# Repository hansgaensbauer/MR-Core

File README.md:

### __Quick Start:__ The [software](/software) folder contains a template Jupyter Notebook and documentation for the MRC class. 

# MR-Core
An FPGA Driven DAC + ADC for Magnetic Resonance, intended as a capable controller for Magnetic Resonance Imaging and Magnetic Resonance Relaxometry. 

### Features
- STM32F767 Microcontroller for experiment-level sequencing and backend signal processing
- Artix 7 FPGA for pulse generation, digital downconversion and DSP
- 500MSps dual oversampling DAC with on-chip NCO for RF pulse synthesis
- 120MSps dual ADC
- X, Y, and Z gradient drivers for 3A low impedance gradient coils
- 5Gbps USB-3.0 controller for raw data extraction
- 100/10 Ethernet 
- SD Card Interface
- Magnet/switch interface for temperature control and T/R switching

# User Manual

## Repository Setup and Software Prerequisites
### Required Software
- [KiCAD EDA](https://www.kicad.org/)
- [STM32CubeIDE](https://www.st.com/en/development-tools/stm32cubeide.html)
    - [STM32CubeF7 Package](https://www.st.com/en/embedded-software/stm32cubef7.html) Version 1.7.1 or 1.7.2
    - ARM CMSIS 5.4.0
- [AMD Vivado](https://www.xilinx.com/products/design-tools/vivado.html)

</br>
To set up the KiCAD Libraries:

- Open KiCAD, go to Preferences -> Configure Paths..., and add a new Environment Variable called "BioMEMS" that points to the hardware/Library folder. 
- Add the symbol library by selecting Preferences -> Manage Symbol Libraries... and selecting the BioMEMS.kicad_sym file in this folder. 
- Check that the library path shows up as "${BioMEMS}.kicad_sym". 
- Add the footprint library by selecting Preferences -> Manage Footprint Libraries... and selecting the BioMEMS.pretty folder in Library. 
- Check that the library path uses the ${BioMEMS} variable.

</br>
The STM32CubeIDE project requires similar setup:

- Create an environment variable called STM32CUBE_REPO, pointed to the STM32Cube\Repository folder on your computer.
- Restart your computer
- Open the project in STM32CubeIDE, and navigate to the IOC file
- Under "Software Packs", click "Manage Software Packs"
- Click "From URL", then "New"
- Add the URL "https://raw.githubusercontent.com/STMicroelectronics/STM32CubeF7/master/Drivers/CMSIS/ARM.CMSIS.pdsc"
- Click "OK" (several times) to add the software pack.
- You may have to close and reopen the "Manage Software Packs" window
- Click the "ARM" tab, and check "CMSIS 5.4.0"
- Click "OK" to close the window, then click "Select Components" under "Software Packs"
- Expand ARM.CMSIS, and check "CMSIS Core - 5.1.2" and "CMSIS DSP 1.5.2" 
- Click OK
- Under Middleware and Software Packs, click "CMSIS", and make sure both CMSIS Core and DSP are checked in the panel that opens
- Save the IOC and rebuild the code
- To add the STM32CubeF7 repository, extract the STM32CubeF7 to the STM32CUBE_REPO folder (next to "Packs")
- Pull the STM32Cube_FW_F7_V1.17.X folder out so it's at the same level as the Packs folder. Check that the path to this folder matches the include paths in Project->Properties (you may have to rename the folder or adjust the paths).

## Hardware Description
### Open Assembly

### PCB Connector Diagram

## Powering On
The MR-Core is designed to work with a 13.8V DC power supply, such as those sold by [Astron Corporation](https://www.astroncorp.com/). These are commonly used for amateur radio, but any linear power supply capable of providing 10A continuously is suitable. If the gradients are not used, only 3A are required. The power connector is a [ASMPR45-1X2-RK](https://www.digikey.com/en/products/detail/anderson-power-products-inc/ASMPR45-1X2-RK/13150596) from [Anderson Power Products, Inc.](https://www.andersonpower.com/us/en.html).

## Programming
### Programming the Microcontroller
- Connect an ST-Link programmer to the STM32 SWD port on the MRC. 
- Flash using STM32CubeIDE

### Programming the FPGA
- Connect an AMD compatible JTAG cable to the FPGA JTAG port on the MRC.
- Open the Hardware Manager in Vivado
- Click "Auto Connect"
- Click "Program" and select the .bit file for the FPGA

### Programming the SPI Flash
By default, new designs programmed into the FPGA must be reprogrammed every time the device loses power. To allow the FPGA image to persist between reboots, a SPI configuration flash is included that can program the FPGA with a default image on startup. To change this default image:
- Right click on create bitstream
- Click "bitstream settings"
- Check the ".bin" option
- Click Apply
- Generate the bitstream
- Click "Add Configuration Memory Device"
- If prompted, search for and select "IS25LP256"
- Right click on the device
- Click "Program"
- find .bin file in runs->impl_1 folder
- Select "Pull-Ups"
- Select the "Erase", "Program", and "Verify" options
- Select Apply, OK
- Disconnect the programming cable and restart the FPGA.

To program the SPI flash without changing the configuration (which you will want to do in most cases to update the FPGA image), the steps are more simple.
- In the Hardware Manager, right click on the SPI Flash in the Hardware window.
- Click "Program Configuration Memory Device"

## Analog Frontend (AFE)
The AFE for the MRC consists of two SXLP-21.4+ lowpass filters and two ZX60-43-S+ gain block amplifiers for the receive side, and one ZX60-100VHX+ amplifier for transmit. The amplifiers are powered by connectors from the MRC PCB, and should not be used with the heatsink removed. The transmit amplifier may be destroyed if it transmits into a poorly tuned or disconnected probe. For development, the transmit port of the MRC should be connected to a 50 ohm termination. The filters can be bypassed by soldering an 0603 resistor onto the jumpers on the filter PCBs. The MRC AFE is intended to be used with an external switch and preamplifier located on the probe - the gain blocks are not low noise amplifiers. 

## Magnet Interface
The magnet interface is connected to the MRC using an ethernet cable. The interface exposes FPGA IO for switching, as well as 3.3V power and microcontroller IO for general use. 

## Gradients
The gradients use 1/4" TRS audio connectors. Do not use 1/4" mono connectors, and do not insert or remove the connectors for the gradients when the board is powered. Doing so can damage the gradient drivers. The gradients are driven by H-bridge circuits to the supply voltage, current limited to 3A by three power resistors on the board. For this reason, neither contact for the gradients (Tip or Ring) is grounded. The Shield should not be connected to the gradient coil.

## USB 3.0
Support for direct baseband sample streaming with Steam-O-Scope firmware from [Joseph Feld](https://github.com/JosephFeld).

## Switch/Preamplifier Module

In order to make it possible to use non-MRC compatible probes with the MRC, a switch and preamplifier module is provided. This module provides about 10dB of gain and it includes a ZX80-DR230-S+ absorbtive RF switch. The truth table for the switch is:
| SW[1]  | SW[0] | Switch State |
| ------------- | ------------- | ----- |
| 0  | 0  | Both Off |
| 0  | 1  | Receive |
| 1  | 0  | Transmit |
| 1  | 1  | Unknown |

The yellow LED on the preamplifier module ethernet connector indicates the status of the transmit switch (on = closed) and the green LED likewise indicates the status of the receive switch.

## MRR-Core Image
This image implements a general purpose, programmable controller for MRI sequences. 

The system is programmed by the STM32 over SPI, and each SPI transaction is 16 bits with the MSB first. There are three types of SPI command: control register programming, frequency tuning word programming, and sequence programming. 

The control register is used for general purpose control of the FPGA, and can be accessed with a SPI transaction where bits [15:14] are `0b10`. The 8 LSBs give the new control register value. The control register is shown below:
**CMD (Opcode `0b00`)**
```
[  7  |  6  |  5  |  4  |  3  |  2  |  1  |  0  ]
[ RST |     |     |     |     |     |TRIG |     ]
```

To program the 16 bit frequency tuning word, the system must first be put into frequency tuning mode by sending the frequency tuning command `0xC000`. The frequency tuning word is sent on the next transaction, and the system will automatically return to IDLE afterward.

To enter sequence programming, the sequence programming command must be sent with the number of lines in the sequence program. The programming command starts with `0b00`, and the 14 LSBs are the number of 16 bit instructions in the sequence.

### MRC Instruction Set
The MRC uses a very simple instruction set designed for precise execution of any pulse sequences. There are four instructions:

**CMD (Opcode `0b00`)**
```
[ 15 | 14 | 13 | 12 | 11 | 10 |  9 |  8 |  7 |  6 |  5 |  4 |  3 |  2 |  1 |  0 ]
[  0 |  0 |   AMP   |  PHASE  |   GRX   |   GRY   |   GRZ   |      RESERVED     ]
```
Change the transmitter amplitude and phase to the values indexed by AMP and PHASE. Set the gradients to the values set by GR[xyz].

**LSET (Opcode `0b01`)**
```
[ 15 | 14 | 13 | 12 | 11 | 10 |  9 |  8 |  7 |  6 |  5 |  4 |  3 |  2 |  1 |  0 ]
[  0 |  1 | COUNTER |                          VALUE                            ]
```
Set COUNTER to VALUE.

**JMP (Opcode `0b10`)**
```
[ 15 | 14 | 13 | 12 | 11 | 10 |  9 |  8 |  7 |  6 |  5 |  4 |  3 |  2 |  1 |  0 ]
[  1 |  0 | COUNTER |                         ADDRESS                           ]
```
If COUNTER is not zero, jump to the absolute ADDRESS. If COUNTER is zero, set COUNTER to `0xFFFF` and advance the instruction counter.

**HALT (Opcode `0b11`)**
```
[ 15 | 14 | 13 | 12 | 11 | 10 |  9 |  8 |  7 |  6 |  5 |  4 |  3 |  2 |  1 |  0 ]
[  1 |  1 |                                                                     ]
```
Terminates the sequence.

To better compress the immediates for programming amplitude and phase so that all of the pulse parameters can be updated simultaneously, the AMP and PHASE fields in the CMD instruction do not directly specify the amplitude or phase, but instead give the address of the correct value within separate lookup tables that are programmed with the sequence. The first four lines of the sequence program are the four amplitude fields, and the second four lines are the four phase fields. 

### Digital Downconversion
The 120MSps data stream from the ADC is too much data for the STM32 to process, and most of this data is useless as it covers frequencies far away from the Larmor frequency of the magnet. To lower the data rate and isolate only a certain band of interest, the FPGA can digitally downconvert and downsample the ADC data stream. The digital design responsible for this is contained in the "mrr-ddc" block design within the MR-Core Vivado project. 

The structure of the DDC is shown in the HDL block diagram above. The parallel data is converted to AXI by the adc_to_axi module. This is fed into the mrr-ddc block design, which includes a complex multiplier and direct digital synthesizer for downconversion. The frequency shifted products are filtered and passed to a FIFO, before being passed to the STM32 using the STM32 Flexible Memory Controller (FMC).

The layout of the digital filter is shown below:

This filter is responsible for both decimation and the bulk of noise rejection, so the performance requirements are strict. The filter is implemented in several stages so that the high complexity FIR filters at the end see only data streams that are already significantly decimated (the final FIR filter sees an input data rate of 1MSa/s, compared to 120MSa/s for the CIC decimator).

The filter design is done in Matlab, and the current design is captured by filtdesign.m in MR-Core->hdl->Utilities. The transfer function is shown below (x axes in MHz):

## Firmware
The firmware running on the STM32 is responsible for processing or passing the data stream from the FPGA during receive, and also for configuring the FPGA, the DAC, and the ADC. The mrc STM32CubeIDE project in the "firmware" folder provides C drivers for the DAC, the ADC, and an "MRC" driver that handles communication with the FPGA, pulse sequencing, and data streaming. The DAC and ADC drivers provide access to the test patterns, power down states, and programming registers for these chips.

For USB 2.0 Full speed data streaming, the `Transfer_Buffer()` function in mrc.c will coordinate FMC reads into a ping-pong buffer that is then emptied over the USB CDC hardware into a PC. A basic serial command interface is available in this demo so that a user can trigger pulse-echo sequences by sending the command `pulseecho` over USB CDC.

## Software and UI
### Pulseq Compiler
A limited Pulseq compiler is provided in `software`. This program requires pypulseq to run, however, the latest stable release of pypulseq cannot run with the most recent versions of numpy. This can be solved by replacing every instance of `np.float` and `np.complex` in the sigpy and pypulseq libraries with `float` and `complex` respectively. 

To run the compiler, use `py mrc_pulseq_assembler.py [sequence_file.seq]` where `[sequence_file.seq]` is replaced by the path to your pulseq file. This will generate a .mrc file with the machine code for the MRI. To facilitate debugging, a objdump-style disassembler is also provided. To run the disassembler, use `py mrcdump.py [mrc_file.mrc]` where `[mrc_file.mrc]` is replaced with the path to your .mrc file. It will produce an output in the following format:

```
Statics:
Phase 0: 0
Phase 1: 0
Phase 2: 0
Phase 3: 0

Amp 0: 0
Amp 1: 28000
Amp 2: 56000
Amp 3: 0

Instructions:
0:      0001000000000000        cmd     1 0 00 00 00
1:      0100010010101111        lset    0 1199
...     ...                     ...     ...
20:     0000000000000000        cmd     0 0 00 00 00
21:     1100000000000000        halt.
```

For the system demo, a python driver for the MRC board is available in the "software" folder. bioreactormonitoring.py uses this driver to periodically acquire pulsecho sequences and plot the received data and extracted T2 values on an animated graph on the computer.

## Contributing
Best practices: make your own branch!

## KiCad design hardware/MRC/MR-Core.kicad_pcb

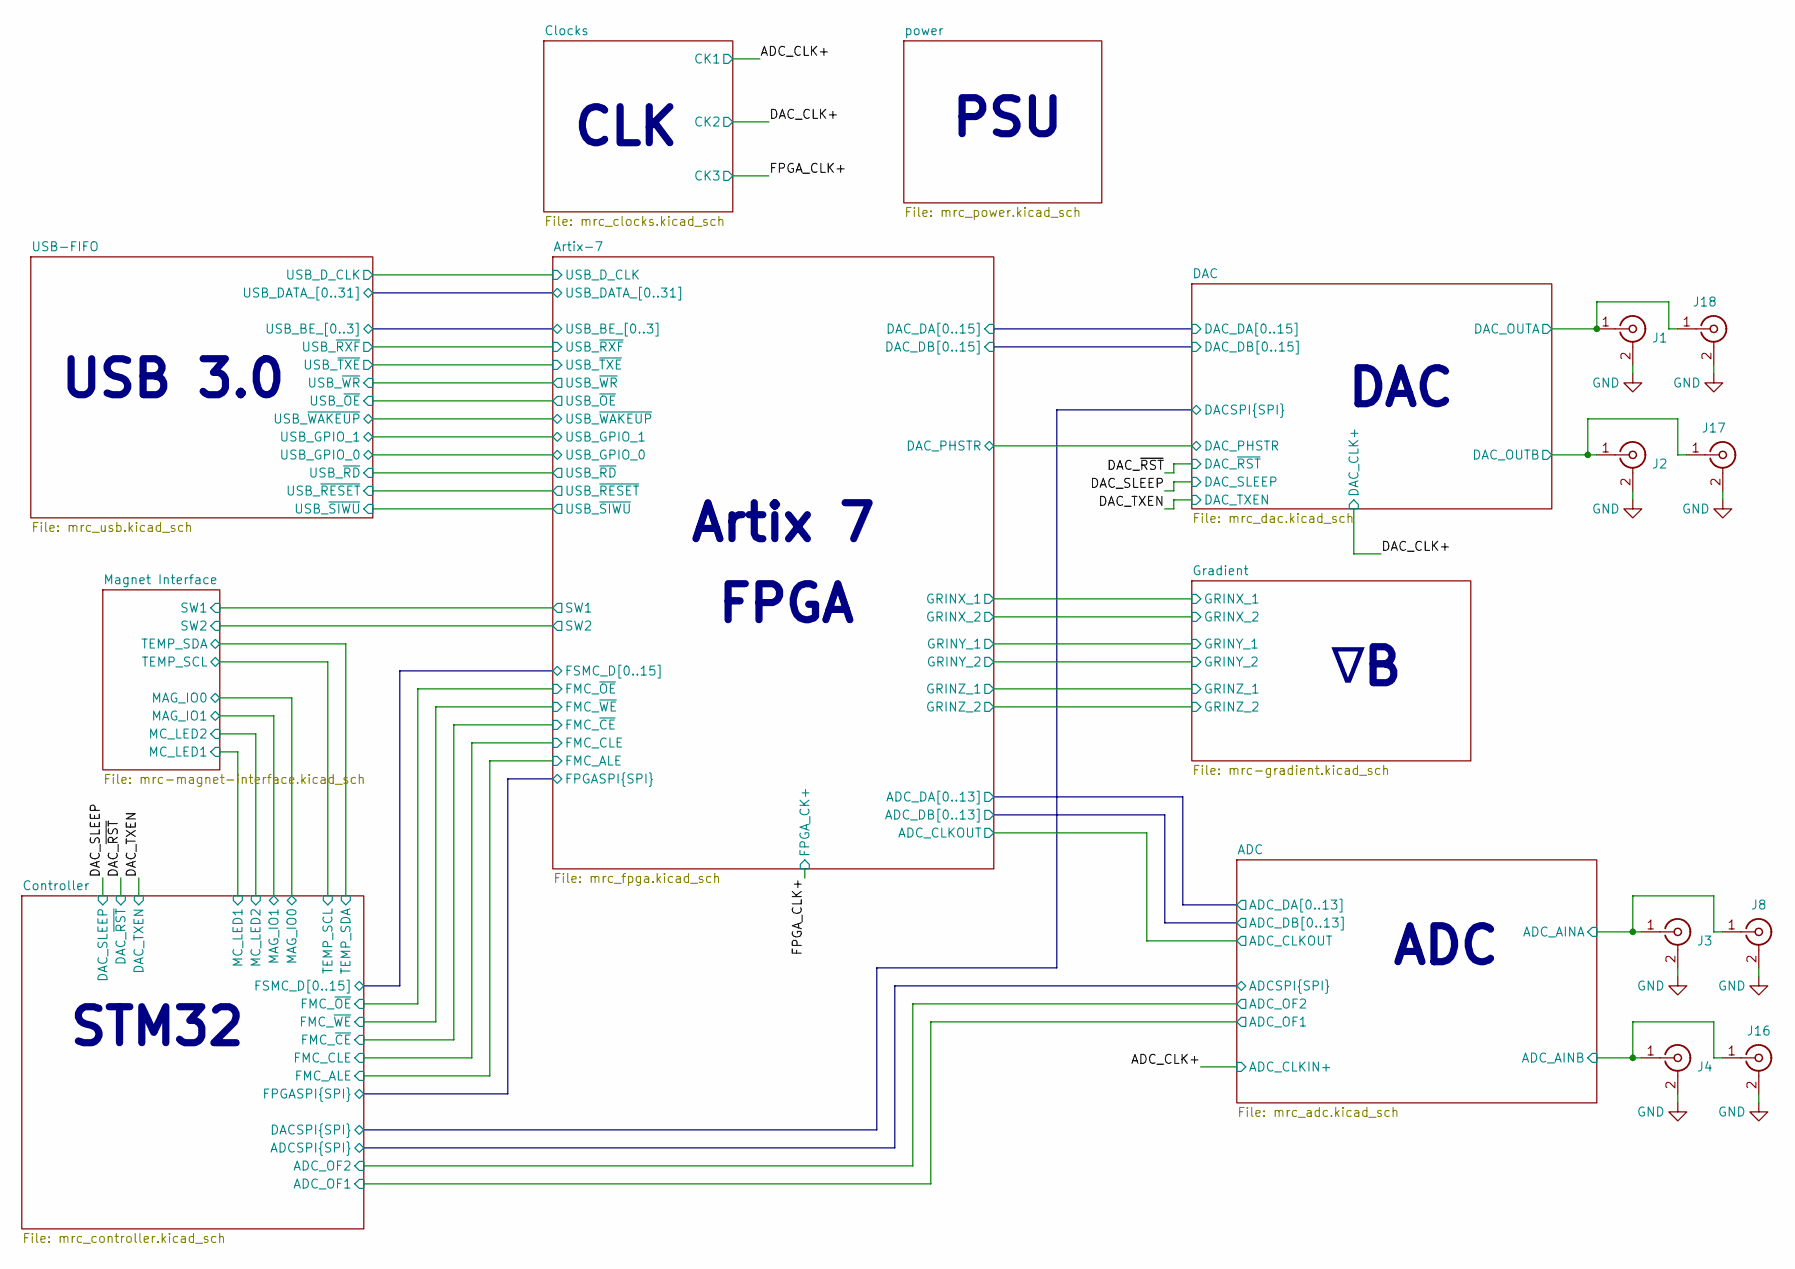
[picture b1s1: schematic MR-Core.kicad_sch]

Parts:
J1, J2, J3, J4: Conn_Coaxial; MMCX_Molex_73415-1471_Vertical; MPN C588477
J8, J16, J17, J18: Conn_Coaxial; SMA_Samtec_SMA-J-P-X-ST-EM1_EdgeMount; MPN C588477

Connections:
/ADC/ADC_AINA: J3.1 (In), J8.1 (In); also elsewhere on the board
/ADC/ADC_AINB: J4.1 (In), J16.1 (In); also elsewhere on the board
/DAC/DAC_OUTA: J1.1 (In), J18.1 (In); also elsewhere on the board
/DAC/DAC_OUTB: J2.1 (In), J17.1 (In); also elsewhere on the board

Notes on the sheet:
FPGA
USB 3.0
ADC
Artix 7
STM32
CLK
DAC
PSU

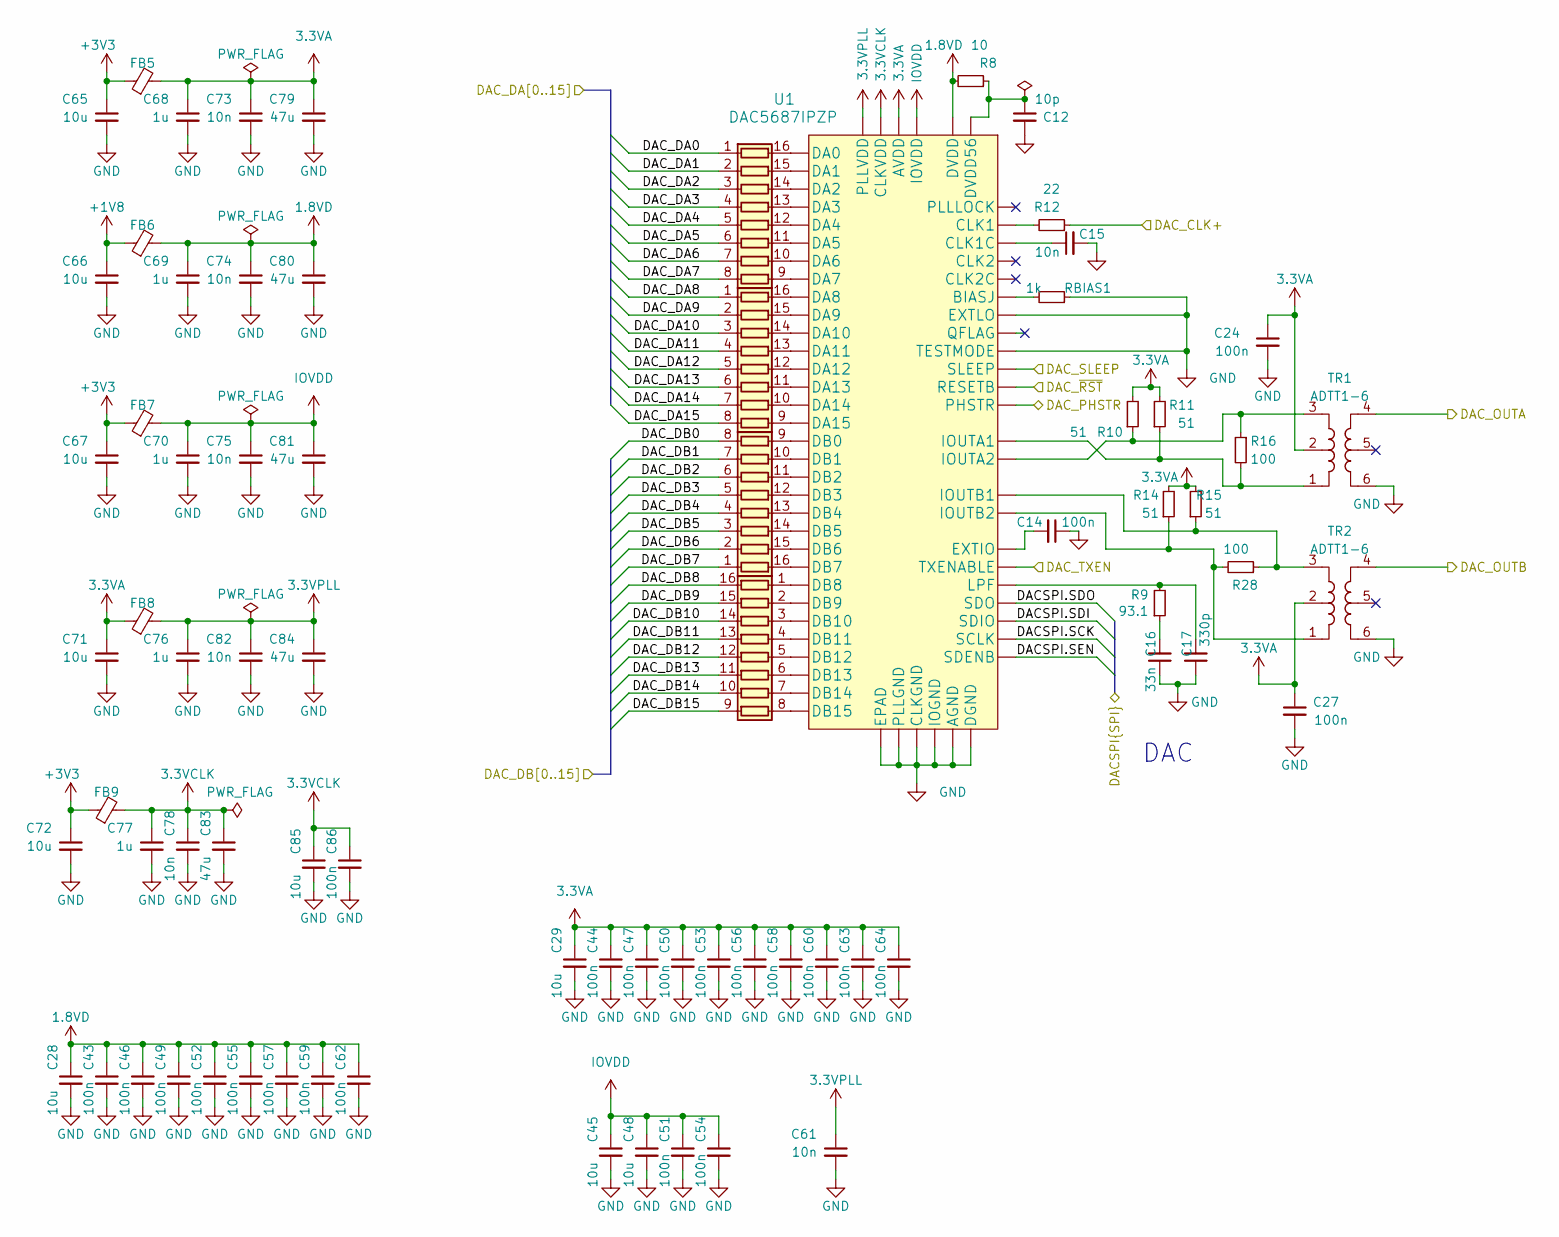
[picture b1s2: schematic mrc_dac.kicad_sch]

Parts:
C12: 10p; C_0603_1608Metric; MPN C1634
C14, C24, C27, C43, C44, C46, C47, C49, C50, C51, C52, C53, C54, C55, C56, C57, C58, C59, C60, C62, C63, C64, C86: 100n; C_0603_1608Metric; MPN C14663
C15, C61, C73, C74, C75, C78, C82: 10n; C_0603_1608Metric; MPN C57112
C16: 33n; C_0603_1608Metric; MPN C21117
C17: 330p; C_0603_1608Metric; MPN C1664
C28, C29, C45, C48, C65, C66, C67, C71, C72, C85: 10u; C_0603_1608Metric; MPN C96446
C68, C69, C70, C76, C77: 1u; C_0603_1608Metric; MPN C15849
C79, C80, C81, C83, C84: 47u; C_0603_1608Metric; MPN C318632
FB5, FB6, FB7, FB8, FB9: FerriteBead_Small; L_0603_1608Metric; MPN C14709
R8: 10; R_0603_1608Metric; MPN C22859
R9: 93.1; R_0603_1608Metric; MPN C23132
R10, R11, R14, R15: 51; R_0603_1608Metric; MPN C23197
R12: 22; R_0603_1608Metric; MPN C23345
R16, R28: 100; R_0603_1608Metric; MPN C22775
RBIAS1: 1k; R_0603_1608Metric; MPN C21190
RN3, RN4, RN5, RN6: EXB-2HV470JV; CAY16-470J8LF; MPN C713462
TR1, TR2: ADTT1-6; Mini-Circuits_CD637_H5.23mm; MPN C6495091
U1: DAC5687IPZP; TQFP-100-1EP_14x14mm_P0.5mm_EP5x5mm_ThermalVias_Large; MPN C1554572

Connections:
1.8VD: C28.1, C43.1, C46.1, C49.1, C52.1, C55.1, C57.1, C59.1, C62.1, C69.1, C74.1, C80.1, FB6.2, R8.2, U1.26 (DVDD), U1.32 (DVDD), U1.37 (DVDD), U1.44 (DVDD), U1.68 (DVDD), U1.82 (DVDD), U1.89 (DVDD), U1.100 (DVDD)
3.3VA: C24.1, C27.1, C29.1, C44.1, C47.1, C50.1, C53.1, C56.1, C58.1, C60.1, C63.1, C64.1, C68.1, C71.1, C73.1, C79.1, FB5.2, FB8.1, R10.2, R11.2, R14.2, R15.2, TR1.2, TR2.2, U1.2 (AVDD), U1.3 (AVDD), U1.8 (AVDD), U1.10 (AVDD), U1.14 (AVDD), U1.16 (AVDD), U1.18 (AVDD), U1.23 (AVDD), U1.24 (AVDD)
3.3VCLK: C77.1, C78.1, C83.1, C85.1, C86.1, FB9.2, U1.61 (CLKVDD)
3.3VPLL: C61.1, C76.1, C82.1, C84.1, FB8.2, U1.67 (PLLVDD)
+1V8: C66.1, FB6.1; also elsewhere on the board
+3V3: C65.1, C67.1, C72.1, FB5.1, FB7.1, FB9.1; also elsewhere on the board
/Artix-7/DAC_DA0: RN4.1 (R1.1); also elsewhere on the board
/Artix-7/DAC_DA1: RN4.2 (R2.1); also elsewhere on the board
/Artix-7/DAC_DA2: RN4.3 (R3.1); also elsewhere on the board
/Artix-7/DAC_DA3: RN4.4 (R4.1); also elsewhere on the board
/Artix-7/DAC_DA4: RN4.5 (R5.1); also elsewhere on the board
/Artix-7/DAC_DA5: RN4.6 (R6.1); also elsewhere on the board
/Artix-7/DAC_DA6: RN4.7 (R7.1); also elsewhere on the board
/Artix-7/DAC_DA7: RN4.8 (R8.1); also elsewhere on the board
/Artix-7/DAC_DA8: RN5.1 (R1.1); also elsewhere on the board
/Artix-7/DAC_DA9: RN5.2 (R2.1); also elsewhere on the board
/Artix-7/DAC_DA10: RN5.3 (R3.1); also elsewhere on the board
/Artix-7/DAC_DA11: RN5.4 (R4.1); also elsewhere on the board
/Artix-7/DAC_DA12: RN5.5 (R5.1); also elsewhere on the board
/Artix-7/DAC_DA13: RN5.6 (R6.1); also elsewhere on the board
/Artix-7/DAC_DA14: RN5.7 (R7.1); also elsewhere on the board
/Artix-7/DAC_DA15: RN5.8 (R8.1); also elsewhere on the board
/Artix-7/DAC_DB0: RN6.8 (R8.1); also elsewhere on the board
/Artix-7/DAC_DB1: RN6.7 (R7.1); also elsewhere on the board
/Artix-7/DAC_DB2: RN6.6 (R6.1); also elsewhere on the board
/Artix-7/DAC_DB3: RN6.5 (R5.1); also elsewhere on the board
/Artix-7/DAC_DB4: RN6.4 (R4.1); also elsewhere on the board
/Artix-7/DAC_DB5: RN6.3 (R3.1); also elsewhere on the board
/Artix-7/DAC_DB6: RN6.2 (R2.1); also elsewhere on the board
/Artix-7/DAC_DB7: RN6.1 (R1.1); also elsewhere on the board
/Artix-7/DAC_DB8: RN3.16 (R1.2); also elsewhere on the board
/Artix-7/DAC_DB9: RN3.15 (R2.2); also elsewhere on the board
/Artix-7/DAC_DB10: RN3.14 (R3.2); also elsewhere on the board
/Artix-7/DAC_DB11: RN3.13 (R4.2); also elsewhere on the board
/Artix-7/DAC_DB12: RN3.12 (R5.2); also elsewhere on the board
/Artix-7/DAC_DB13: RN3.11 (R6.2); also elsewhere on the board
/Artix-7/DAC_DB14: RN3.10 (R7.2); also elsewhere on the board
/Artix-7/DAC_DB15: RN3.9 (R8.2); also elsewhere on the board
/Artix-7/DAC_PHSTR: U1.94 (PHSTR); also elsewhere on the board
/Controller/DACSPI.SCK: U1.29 (SCLK); also elsewhere on the board
/Controller/DACSPI.SDI: U1.30 (SDIO); also elsewhere on the board
/Controller/DACSPI.SDO: U1.31 (SDO); also elsewhere on the board
/Controller/DACSPI.SEN: U1.28 (SDENB); also elsewhere on the board
/DAC/DAC_OUTA: TR1.4; also elsewhere on the board
/DAC/DAC_OUTB: TR2.4; also elsewhere on the board
/DAC_CLK+: R12.1; also elsewhere on the board
/DAC_SLEEP: U1.96 (SLEEP); also elsewhere on the board
/DAC_TXEN: U1.33 (TXENABLE); also elsewhere on the board
/DAC_~RST: U1.95 (RESETB); also elsewhere on the board
IOVDD: C45.1, C48.1, C51.1, C54.1, C70.1, C75.1, C81.1, FB7.2, U1.46 (IOVDD), U1.80 (IOVDD)
unnamed: C16.2, R9.1
unnamed: RN3.1 (R1.1), U1.83 (DB8)
unnamed: RN3.2 (R2.1), U1.84 (DB9)
unnamed: RN3.3 (R3.1), U1.85 (DB10)
unnamed: RN3.4 (R4.1), U1.86 (DB11)
unnamed: RN3.5 (R5.1), U1.87 (DB12)
unnamed: RN3.6 (R6.1), U1.90 (DB13)
unnamed: RN3.7 (R7.1), U1.91 (DB14)
unnamed: RN3.8 (R8.1), U1.92 (DB15)
unnamed: RN4.16 (R1.2), U1.55 (DA0)
unnamed: RN4.15 (R2.2), U1.54 (DA1)
unnamed: RN4.14 (R3.2), U1.53 (DA2)
unnamed: RN4.13 (R4.2), U1.52 (DA3)
unnamed: RN4.12 (R5.2), U1.51 (DA4)
unnamed: RN4.11 (R6.2), U1.50 (DA5)
unnamed: RN4.10 (R7.2), U1.49 (DA6)
unnamed: RN4.9 (R8.2), U1.48 (DA7)
unnamed: RN5.16 (R1.2), U1.43 (DA8)
unnamed: RN5.15 (R2.2), U1.42 (DA9)
unnamed: RN5.14 (R3.2), U1.41 (DA10)
unnamed: RN5.13 (R4.2), U1.40 (DA11)
unnamed: RN5.12 (R5.2), U1.39 (DA12)
unnamed: RN5.11 (R6.2), U1.36 (DA13)
unnamed: RN5.10 (R7.2), U1.35 (DA14)
unnamed: RN5.9 (R8.2), U1.34 (DA15)
unnamed: RN6.16 (R1.2), U1.78 (DB7)
unnamed: RN6.15 (R2.2), U1.77 (DB6)
unnamed: RN6.14 (R3.2), U1.76 (DB5)
unnamed: RN6.13 (R4.2), U1.75 (DB4)
unnamed: RN6.12 (R5.2), U1.74 (DB3)
unnamed: RN6.11 (R6.2), U1.73 (DB2)
unnamed: RN6.10 (R7.2), U1.72 (DB1)
unnamed: RN6.9 (R8.2), U1.71 (DB0)
unnamed: RBIAS1.2, U1.13 (BIASJ)
unnamed: R12.2, U1.59 (CLK1)
unnamed: C15.1, U1.60 (CLK1C)
unnamed: C12.1, R8.1, U1.56 (DVDD56)
unnamed: C14.2, U1.11 (EXTIO)
unnamed: R11.1, R16.2, TR1.1, U1.21 (IOUTA1)
unnamed: R10.1, R16.1, TR1.3, U1.20 (IOUTA2)
unnamed: R15.1, R28.1, TR2.3, U1.5 (IOUTB1)
unnamed: R14.1, R28.2, TR2.1, U1.6 (IOUTB2)
unnamed: C17.2, R9.2, U1.66 (LPF)

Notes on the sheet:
DAC

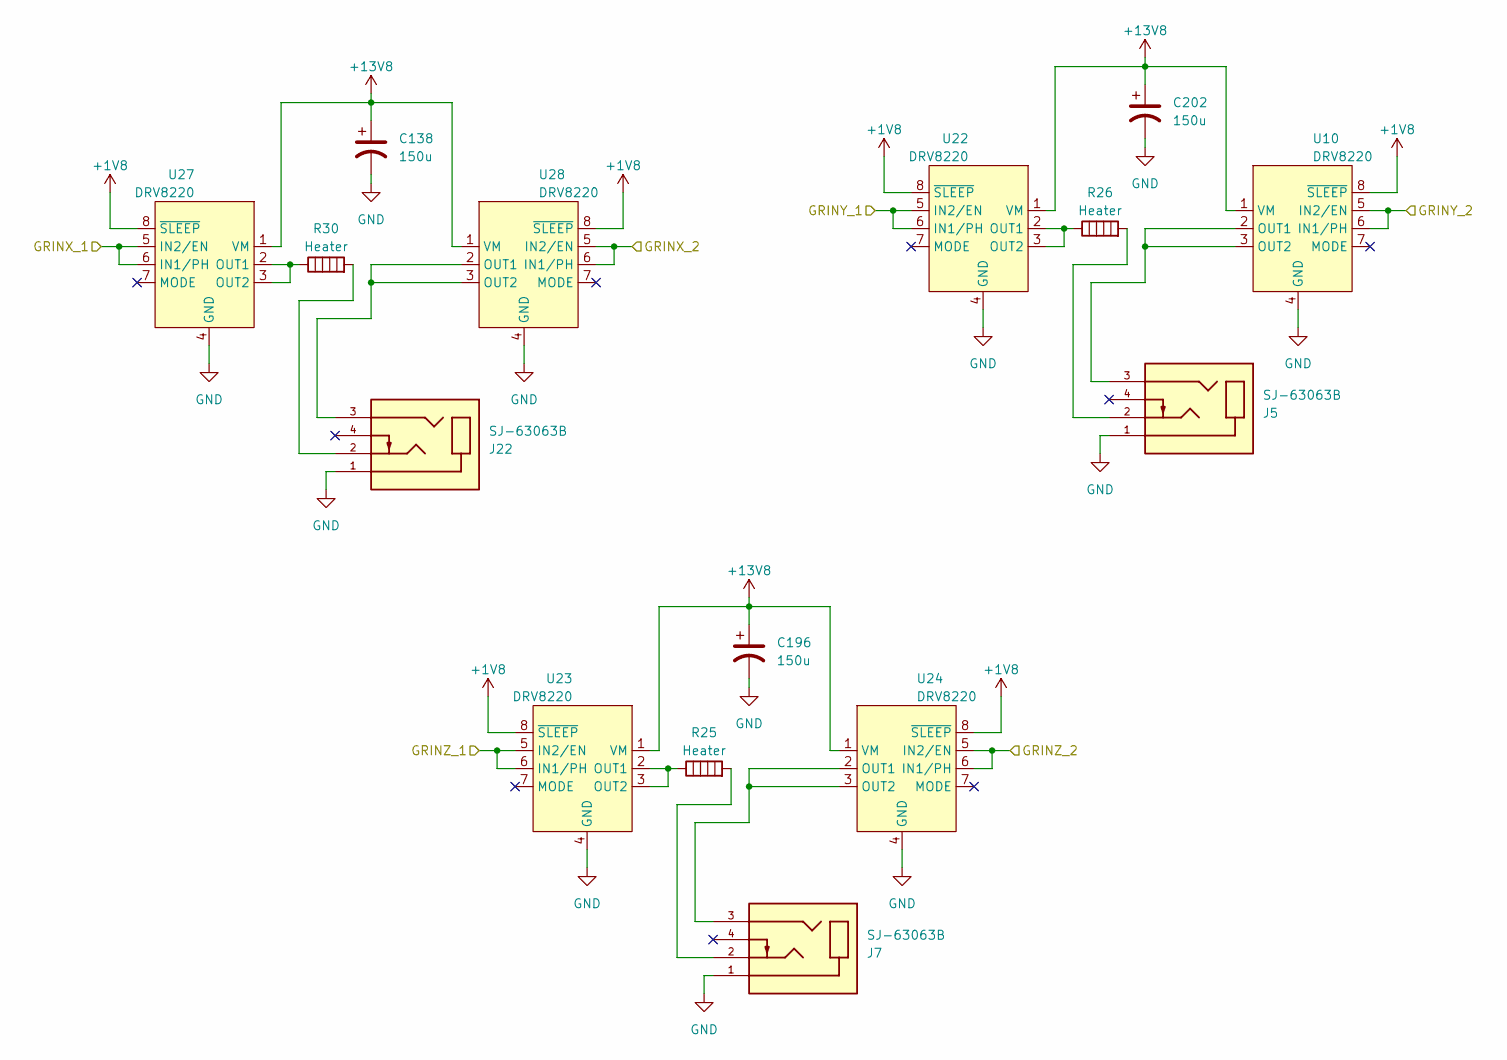
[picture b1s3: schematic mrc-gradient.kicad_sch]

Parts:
C138, C196, C202: 150u; CP_Elec_6.3x5.8; MPN C20040380
J5, J7, J22: SJ-63063B; MPN C4992577
R25, R26, R30: Heater; TO-220-2_BottomHeatsink
U10, U22, U23, U24, U27, U28: DRV8220; WSON-8-1EP_2x2mm_P0.5mm_EP0.9x1.6mm; MPN C3681269

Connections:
+1V8: U10.8 (~SLEEP), U22.8 (~SLEEP), U23.8 (~SLEEP), U24.8 (~SLEEP), U27.8 (~SLEEP), U28.8 (~SLEEP); also elsewhere on the board
+13V8: C138.1, C196.1, C202.1, U10.1 (VM), U22.1 (VM), U23.1 (VM), U24.1 (VM), U27.1 (VM), U28.1 (VM); also elsewhere on the board
/Artix-7/GRINX_1: U27.5 (IN2/EN), U27.6 (IN1/PH); also elsewhere on the board
/Artix-7/GRINX_2: U28.5 (IN2/EN), U28.6 (IN1/PH); also elsewhere on the board
/Artix-7/GRINY_1: U22.5 (IN2/EN), U22.6 (IN1/PH); also elsewhere on the board
/Artix-7/GRINY_2: U10.5 (IN2/EN), U10.6 (IN1/PH); also elsewhere on the board
/Artix-7/GRINZ_1: U23.5 (IN2/EN), U23.6 (IN1/PH); also elsewhere on the board
/Artix-7/GRINZ_2: U24.5 (IN2/EN), U24.6 (IN1/PH); also elsewhere on the board
unnamed: J5.2, R26.2
unnamed: J7.2, R25.2
unnamed: J22.2, R30.2
unnamed: J5.3, U10.2 (OUT1), U10.3 (OUT2)
unnamed: R26.1, U22.2 (OUT1), U22.3 (OUT2)
unnamed: R25.1, U23.2 (OUT1), U23.3 (OUT2)
unnamed: J7.3, U24.2 (OUT1), U24.3 (OUT2)
unnamed: R30.1, U27.2 (OUT1), U27.3 (OUT2)
unnamed: J22.3, U28.2 (OUT1), U28.3 (OUT2)

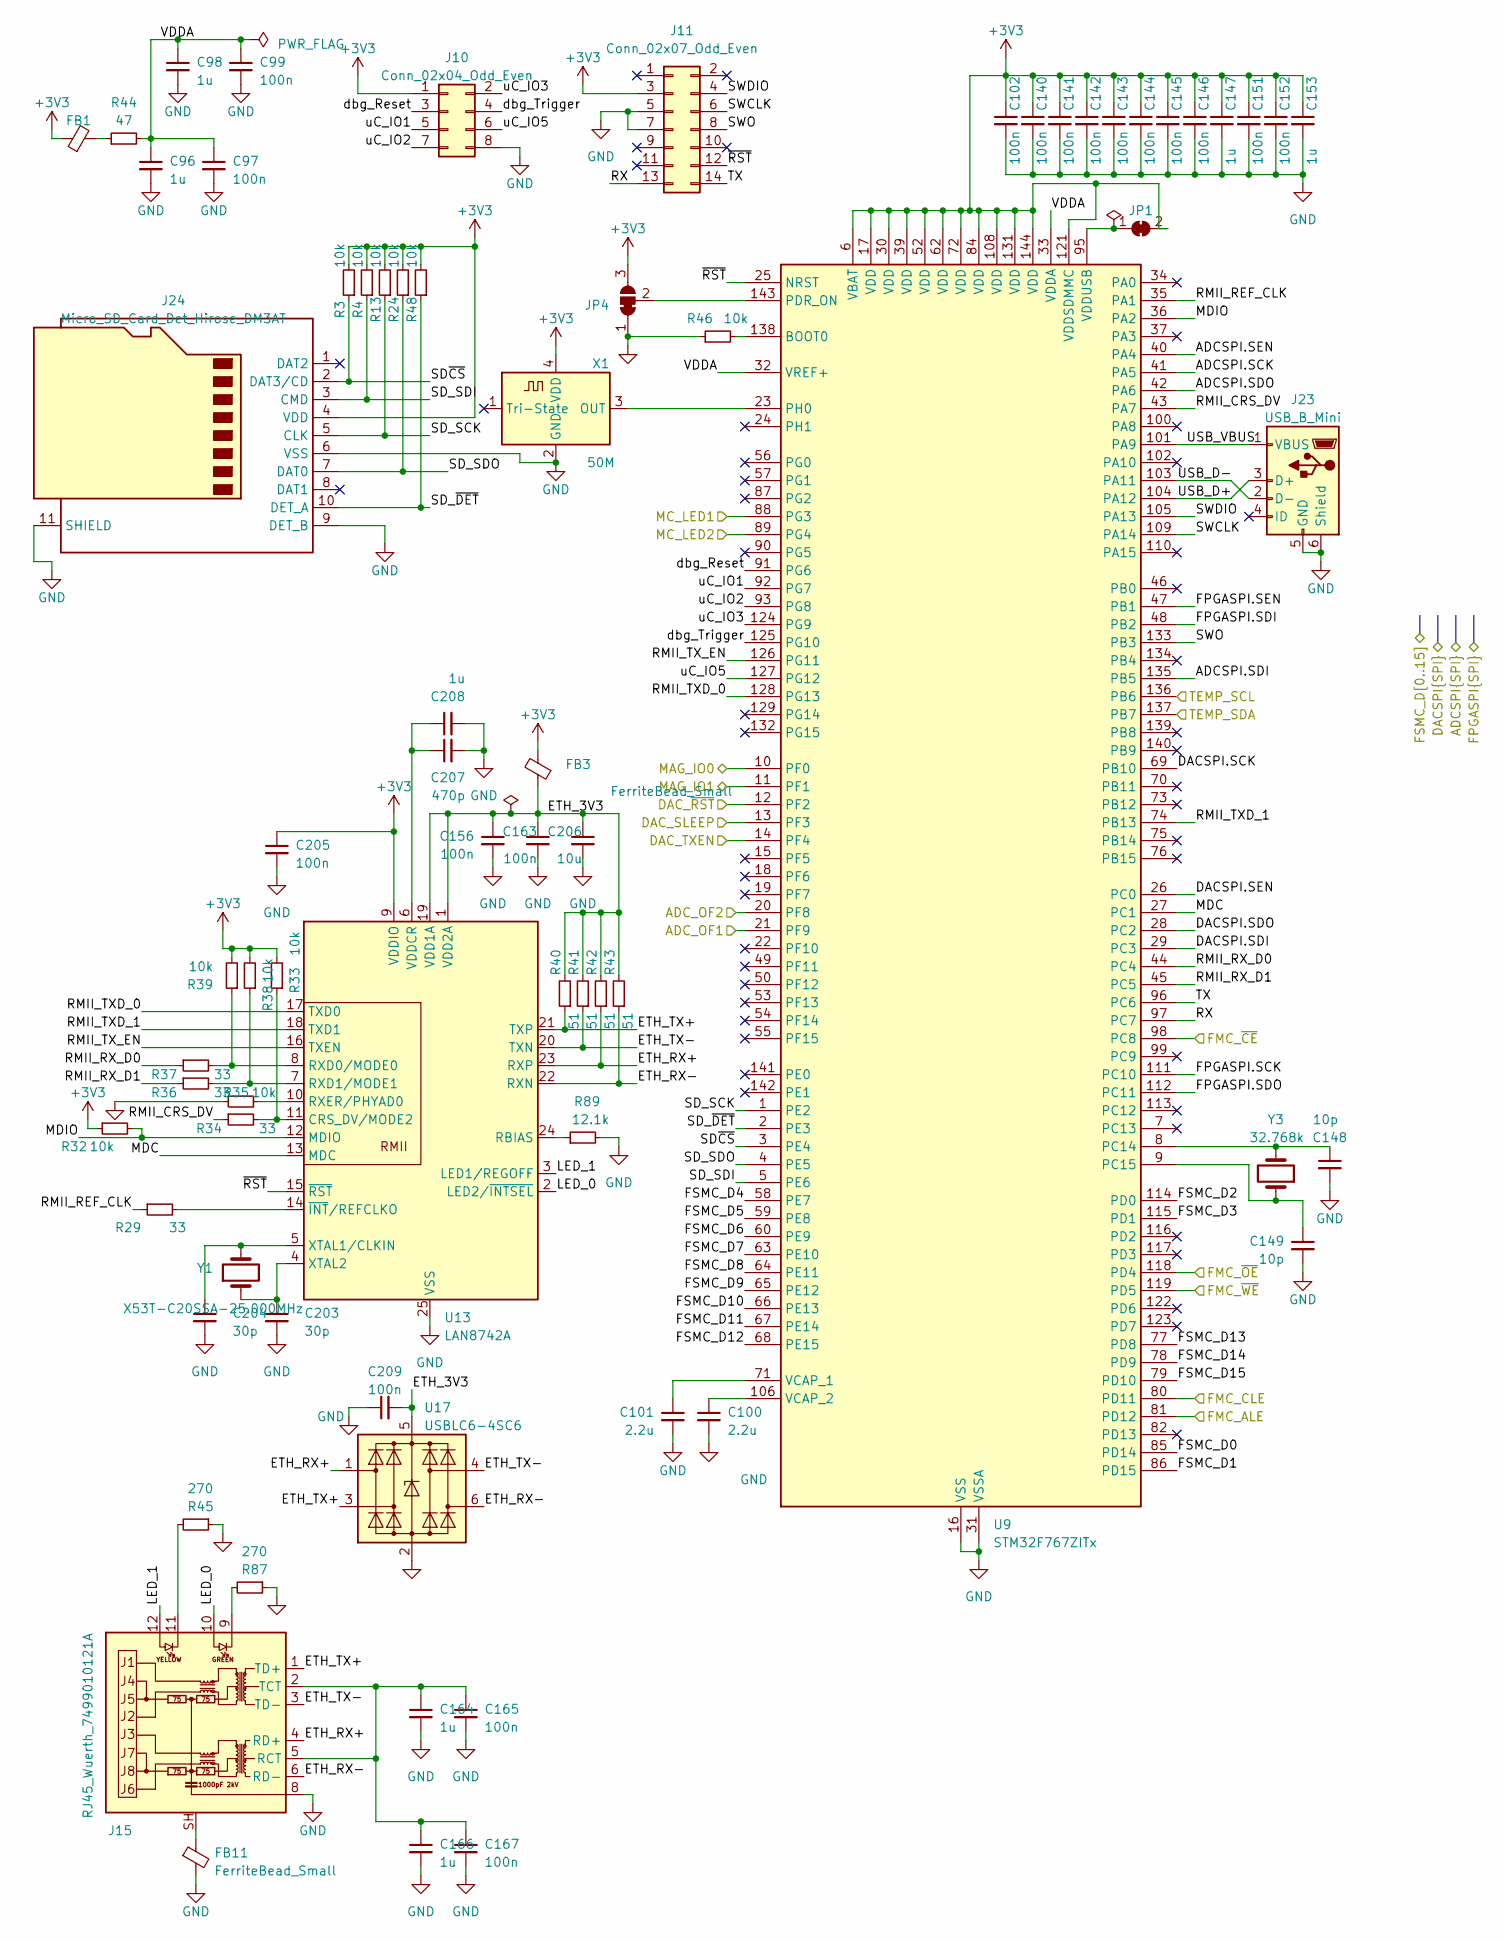
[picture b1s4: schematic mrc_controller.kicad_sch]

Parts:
C96, C98, C147, C153, C164, C166, C208: 1u; C_0603_1608Metric; MPN C15849
C97, C99, C102, C140, C141, C142, C143, C144, C145, C146, C151, C152, C156, C163, C165, C167, C205, C209: 100n; C_0603_1608Metric; MPN C14663
C100, C101: 2.2u; C_0603_1608Metric; MPN C23630
C148, C149: 10p; C_0603_1608Metric; MPN C1634
C203, C204: 30p; C_0603_1608Metric; MPN C1658
C206: 10u; C_0805_2012Metric; MPN C96446
C207: 470p; C_0603_1608Metric; MPN C1620
FB1, FB3, FB11: FerriteBead_Small; L_0603_1608Metric; MPN C14709
J10: Conn_02x04_Odd_Even; PinHeader_2x04_P2.54mm_Vertical
J11: Conn_02x07_Odd_Even; PinHeader_2x07_P1.27mm_Vertical_SMD
J15: RJ45_Wuerth_7499010121A; RJ45_Wuerth_7499010121A_Horizontal; MPN C5451791
J23: USB_B_Mini; USB_Mini-B_Wuerth_65100516121_Horizontal; MPN C5120592
J24: Micro_SD_Card_Det_Hirose_DM3AT; microSD_HC_Hirose_DM3BT-DSF-PEJS; MPN C597972
JP1: SolderJumper_2_Bridged; SolderJumper-2_P1.3mm_Bridged_Pad1.0x1.5mm
JP4: SolderJumper_3_Bridged12; SolderJumper-3_P1.3mm_Bridged2Bar12_Pad1.0x1.5mm
R3, R4, R13, R24, R32, R33, R35, R38, R39, R46, R48: 10k; R_0603_1608Metric; MPN C25804
R29, R34, R36, R37: 33; R_0603_1608Metric; MPN C23140
R40, R41, R42, R43: 51; R_0603_1608Metric; MPN C23197
R44: 47; R_0603_1608Metric; MPN C23182
R45, R87: 270; R_0603_1608Metric; MPN C22966
R89: 12.1k; R_0603_1608Metric; MPN C22864
U9: STM32F767ZITx; LQFP-144_20x20mm_P0.5mm; MPN C90235
U13: LAN8742A; VQFN-24-1EP_4x4mm_P0.5mm_EP2.5x2.5mm_ThermalVias_LargeDrill; MPN C621425
U17: USBLC6-4SC6; SOT-23-6; MPN C5197386
X1: 50M; Oscillator_SMD_ECS_2520MV-xxx-xx-4Pin_2.5x2.0mm; MPN C17348430
Y1: X53T-C20SSA-25.000MHz; Crystal_SMD_MicroCrystal_CM9V-T1A-2Pin_1.6x1.0mm; MPN C717795
Y3: 32.768k; Crystal_SMD_MicroCrystal_CM9V-T1A-2Pin_1.6x1.0mm; MPN C5341287/C5341288

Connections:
+3V3: C102.1, C140.1, C141.1, C142.1, C143.1, C144.1, C145.1, C146.1, C147.1, C151.1, C152.1, C153.1, C205.1, FB1.1, FB3.2, J10.1, J11.3, J24.4 (VDD), JP1.2 (B), JP4.3 (B), R3.2, R4.2, R13.2, R24.2, R32.1, R33.2, R38.2, R39.2, R48.2, U9.6 (VBAT), U9.17 (VDD), U9.30 (VDD), U9.39 (VDD), U9.52 (VDD), U9.62 (VDD), U9.72 (VDD), U9.84 (VDD), U9.108 (VDD), U9.121 (VDDSDMMC), U9.131 (VDD), U9.144 (VDD), U13.9 (VDDIO), X1.4 (VDD); also elsewhere on the board
/ADC/ADCSPI.SCK: U9.41 (PA5); also elsewhere on the board
/ADC/ADCSPI.SDI: U9.135 (PB5); also elsewhere on the board
/ADC/ADCSPI.SDO: U9.42 (PA6); also elsewhere on the board
/ADC/ADCSPI.SEN: U9.40 (PA4); also elsewhere on the board
/ADC/ADC_OF1: U9.21 (PF9); also elsewhere on the board
/ADC/ADC_OF2: U9.20 (PF8); also elsewhere on the board
/Artix-7/FMC_ALE: U9.81 (PD12); also elsewhere on the board
/Artix-7/FMC_CLE: U9.80 (PD11); also elsewhere on the board
/Artix-7/FMC_~CE: U9.98 (PC8); also elsewhere on the board
/Artix-7/FMC_~OE: U9.118 (PD4); also elsewhere on the board
/Artix-7/FMC_~WE: U9.119 (PD5); also elsewhere on the board
/Artix-7/FPGASPI.SCK: U9.111 (PC10); also elsewhere on the board
/Artix-7/FPGASPI.SDI: U9.48 (PB2); also elsewhere on the board
/Artix-7/FPGASPI.SEN: U9.47 (PB1); also elsewhere on the board
/Artix-7/FSMC_D0: U9.85 (PD14); also elsewhere on the board
/Artix-7/FSMC_D1: U9.86 (PD15); also elsewhere on the board
/Artix-7/FSMC_D2: U9.114 (PD0); also elsewhere on the board
/Artix-7/FSMC_D3: U9.115 (PD1); also elsewhere on the board
/Artix-7/FSMC_D4: U9.58 (PE7); also elsewhere on the board
/Artix-7/FSMC_D5: U9.59 (PE8); also elsewhere on the board
/Artix-7/FSMC_D6: U9.60 (PE9); also elsewhere on the board
/Artix-7/FSMC_D7: U9.63 (PE10); also elsewhere on the board
/Artix-7/FSMC_D8: U9.64 (PE11); also elsewhere on the board
/Artix-7/FSMC_D9: U9.65 (PE12); also elsewhere on the board
/Artix-7/FSMC_D10: U9.66 (PE13); also elsewhere on the board
/Artix-7/FSMC_D11: U9.67 (PE14); also elsewhere on the board
/Artix-7/FSMC_D12: U9.68 (PE15); also elsewhere on the board
/Artix-7/FSMC_D13: U9.77 (PD8); also elsewhere on the board
/Artix-7/FSMC_D14: U9.78 (PD9); also elsewhere on the board
/Artix-7/FSMC_D15: U9.79 (PD10); also elsewhere on the board
/Controller/DACSPI.SCK: U9.69 (PB10); also elsewhere on the board
/Controller/DACSPI.SDI: U9.29 (PC3); also elsewhere on the board
/Controller/DACSPI.SDO: U9.28 (PC2); also elsewhere on the board
/Controller/DACSPI.SEN: U9.26 (PC0); also elsewhere on the board
/Controller/ETH_3V3: C156.1, C163.1, C206.1, C209.2, FB3.1, R40.2, R41.2, R42.2, R43.2, U13.1 (VDD2A), U13.19 (VDD1A), U17.5 (VBUS)
/Controller/ETH_RX+: J15.4 (RD+), R42.1, U13.23 (RXP), U17.1 (I/O1)
/Controller/ETH_RX-: J15.6 (RD-), R43.1, U13.22 (RXN), U17.6 (I/O4)
/Controller/ETH_TX+: J15.1 (TD+), R40.1, U13.21 (TXP), U17.3 (I/O2)
/Controller/ETH_TX-: J15.3 (TD-), R41.1, U13.20 (TXN), U17.4 (I/O3)
/Controller/LED_0: J15.10, U13.2 (LED2/~INTSEL)
/Controller/LED_1: J15.12, U13.3 (LED1/REGOFF)
/Controller/MAG_IO0: U9.10 (PF0); also elsewhere on the board
/Controller/MAG_IO1: U9.11 (PF1); also elsewhere on the board
/Controller/MC_LED1: U9.88 (PG3); also elsewhere on the board
/Controller/MC_LED2: U9.89 (PG4); also elsewhere on the board
/Controller/MDC: U9.27 (PC1), U13.13 (MDC)
/Controller/MDIO: R32.2, U9.36 (PA2), U13.12 (MDIO)
/Controller/RMII_CRS_DV: R34.1, U9.43 (PA7)
/Controller/RMII_REF_CLK: R29.1, U9.35 (PA1)
/Controller/RMII_RX_D0: R37.1, U9.44 (PC4)
/Controller/RMII_RX_D1: R36.1, U9.45 (PC5)
/Controller/RMII_TXD_0: U9.128 (PG13), U13.17 (TXD0)
/Controller/RMII_TXD_1: U9.74 (PB13), U13.18 (TXD1)
/Controller/RMII_TX_EN: U9.126 (PG11), U13.16 (TXEN)
/Controller/RX: J11.13, U9.97 (PC7)
/Controller/SD_SCK: J24.5 (CLK), R13.1, U9.1 (PE2)
/Controller/SD_SDI: J24.3 (CMD), R4.1, U9.5 (PE6)
/Controller/SD_SDO: J24.7 (DAT0), R24.1, U9.4 (PE5)
/Controller/SD_~DET: J24.10 (DET_A), R48.1, U9.2 (PE3)
/Controller/SD~CS: J24.2 (DAT3/CD), R3.1, U9.3 (PE4)
/Controller/SWCLK: J11.6, U9.109 (PA14)
/Controller/SWDIO: J11.4, U9.105 (PA13)
/Controller/SWO: J11.8, U9.133 (PB3)
/Controller/TEMP_SCL: U9.136 (PB6); also elsewhere on the board
/Controller/TEMP_SDA: U9.137 (PB7); also elsewhere on the board
/Controller/TX: J11.14, U9.96 (PC6)
/Controller/USB_D+: J23.3 (D+), U9.104 (PA12)
/Controller/USB_D-: J23.2 (D-), U9.103 (PA11)
/Controller/USB_VBUS: J23.1 (VBUS), U9.101 (PA9)
/Controller/VDDA: C96.1, C97.1, C98.1, C99.1, R44.2, U9.32 (VREF+), U9.33 (VDDA)
/Controller/uC_IO0: J10.3, U9.91 (PG6)
/Controller/uC_IO1: J10.5, U9.92 (PG7)
/Controller/uC_IO2: J10.7, U9.93 (PG8)
/Controller/uC_IO3: J10.2, U9.124 (PG9)
/Controller/uC_IO4: J10.4, U9.125 (PG10)
/Controller/uC_IO5: J10.6, U9.127 (PG12)
/Controller/~RST: J11.12, U9.25 (NRST), U13.15 (~RST)
/DAC_SLEEP: U9.13 (PF3); also elsewhere on the board
/DAC_TXEN: U9.14 (PF4); also elsewhere on the board
/DAC_~RST: U9.12 (PF2); also elsewhere on the board
unnamed: FB1.2, R44.1
unnamed: FB11.1, J15.SH
unnamed: J15.9, R87.2
unnamed: J15.11, R45.2
unnamed: C164.1, C165.1, C166.1, C167.1, J15.2 (TCT), J15.5 (RCT)
unnamed: JP1.1 (A), U9.95 (VDDUSB)
unnamed: JP4.2 (C), U9.143 (PDR_ON)
unnamed: R46.2, U9.138 (BOOT0)
unnamed: C148.1, U9.8 (PC14), Y3.2
unnamed: C149.1, U9.9 (PC15), Y3.1
unnamed: U9.23 (PH0), X1.3 (OUT)
unnamed: C101.1, U9.71 (VCAP_1)
unnamed: C100.1, U9.106 (VCAP_2)
unnamed: R33.1, R34.2, U13.11 (CRS_DV/MODE2)
unnamed: R89.1, U13.24 (RBIAS)
unnamed: R37.2, R39.1, U13.8 (RXD0/MODE0)
unnamed: R36.2, R38.1, U13.7 (RXD1/MODE1)
unnamed: R35.2, U13.10 (RXER/PHYAD0)
unnamed: C207.1, C208.1, U13.6 (VDDCR)
unnamed: C204.1, U13.5 (XTAL1/CLKIN), Y1.2
unnamed: C203.1, U13.4 (XTAL2), Y1.1
unnamed: R29.2, U13.14 (~INT/REFCLKO)

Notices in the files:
firmware/mrc/Core/Src/stm32f7xx_hal_msp.c:
Copyright (c) 2024 STMicroelectronics.
All rights reserved.
This software is licensed under terms that can be found in the LICENSE file
